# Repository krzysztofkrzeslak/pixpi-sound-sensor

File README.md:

# pixpi-sound-sensor
Repository which holds sound sensor sources(schematic and board)for PiXPi controller <br/>

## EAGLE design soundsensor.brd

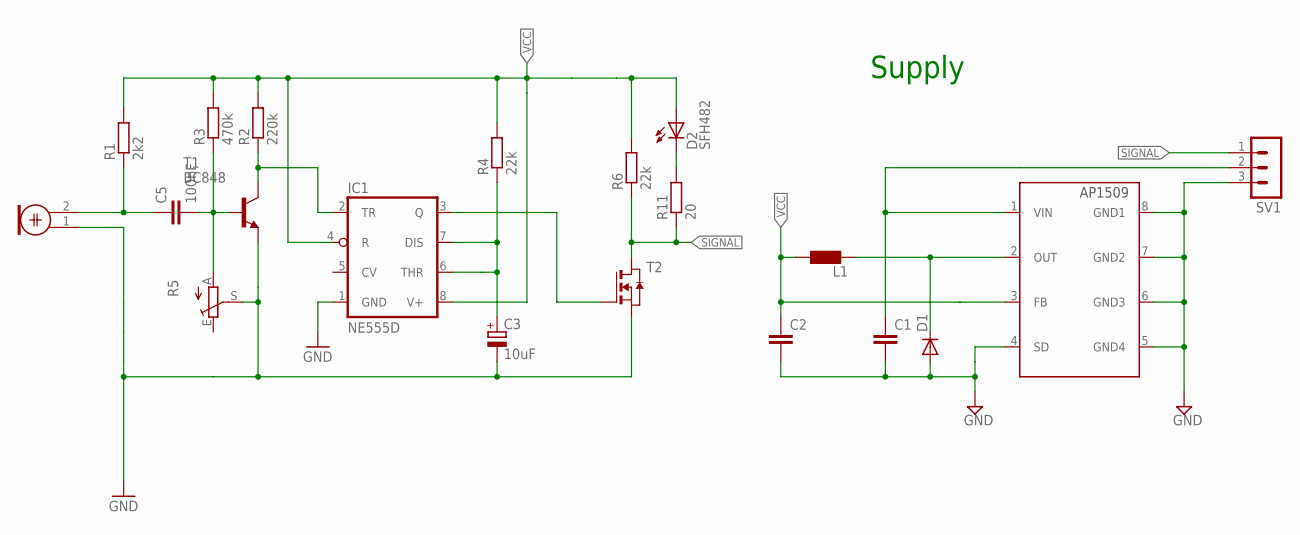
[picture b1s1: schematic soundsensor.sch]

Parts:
C1, C2: C-EUC1210; C1210
C3: 10uF; 150CLZ-1010
C5: 100nF; C0805K
D1: DIODE-SOD323-W; SOD323-W
D2: SFH482
IC1: NE555D; SO08
L1: LL5038P; L5038P
M1: ELECTRET_MICROPHON-WM-61A; WM-61A
R1: 2k2; M0805
R2: 220k; M0805
R3: 470k; M0805
R4, R6: 22k; M0805
R5: TRIM_EU-CA9V; CA9V
R11: 20; M0805
SV1: MA03-1
T1: BC848; SOT23
T2: NMOSSOT23; SOT-23
U$1: AP1509; SOP08

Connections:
GND: C1.2, C2.2, C3.-, D1.A, IC1.1 (GND), M1.1, R5.S, SV1.3, T1.2 (E), T2.2 (S), U$1.4 (SD), U$1.5 (GND4), U$1.6 (GND3), U$1.7 (GND2), U$1.8 (GND1)
unnamed: D2.K (C), R11.2
unnamed: C1.1, SV1.2, U$1.1 (VIN)
unnamed: D1.C, L1.2, U$1.2 (OUT)
unnamed: C5.1, M1.2, R1.1
unnamed: C5.2, R3.1, R5.A, T1.1 (B)
unnamed: IC1.3 (Q), T2.3 (G)
unnamed: IC1.2 (TR), R2.1, T1.3 (C)
unnamed: C3.+, IC1.6 (THR), IC1.7 (DIS), R4.1
SIGNAL: R6.1, R11.1, SV1.1, T2.1 (D)
VCC: C2.1, D2.A, IC1.4 (R), IC1.8 (V+), L1.1, R1.2, R2.2, R3.2, R4.2, R6.2, U$1.3 (FB)

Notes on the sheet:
Supply

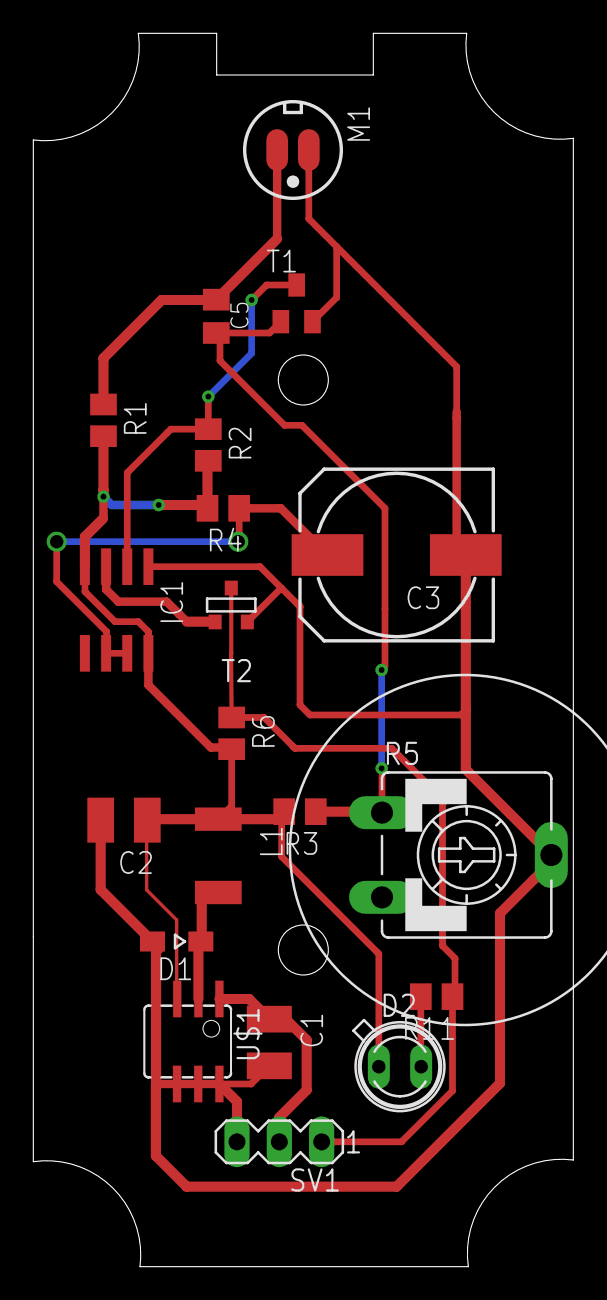
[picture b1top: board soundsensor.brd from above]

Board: 2 copper layers, 32.4 x 74.0 mm, 20 parts (0 on the bottom side), 11 nets.

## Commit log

2019-08-23 Added source schematic and board design for sound sensor intended for pixpi controller
2019-08-23 added board image
